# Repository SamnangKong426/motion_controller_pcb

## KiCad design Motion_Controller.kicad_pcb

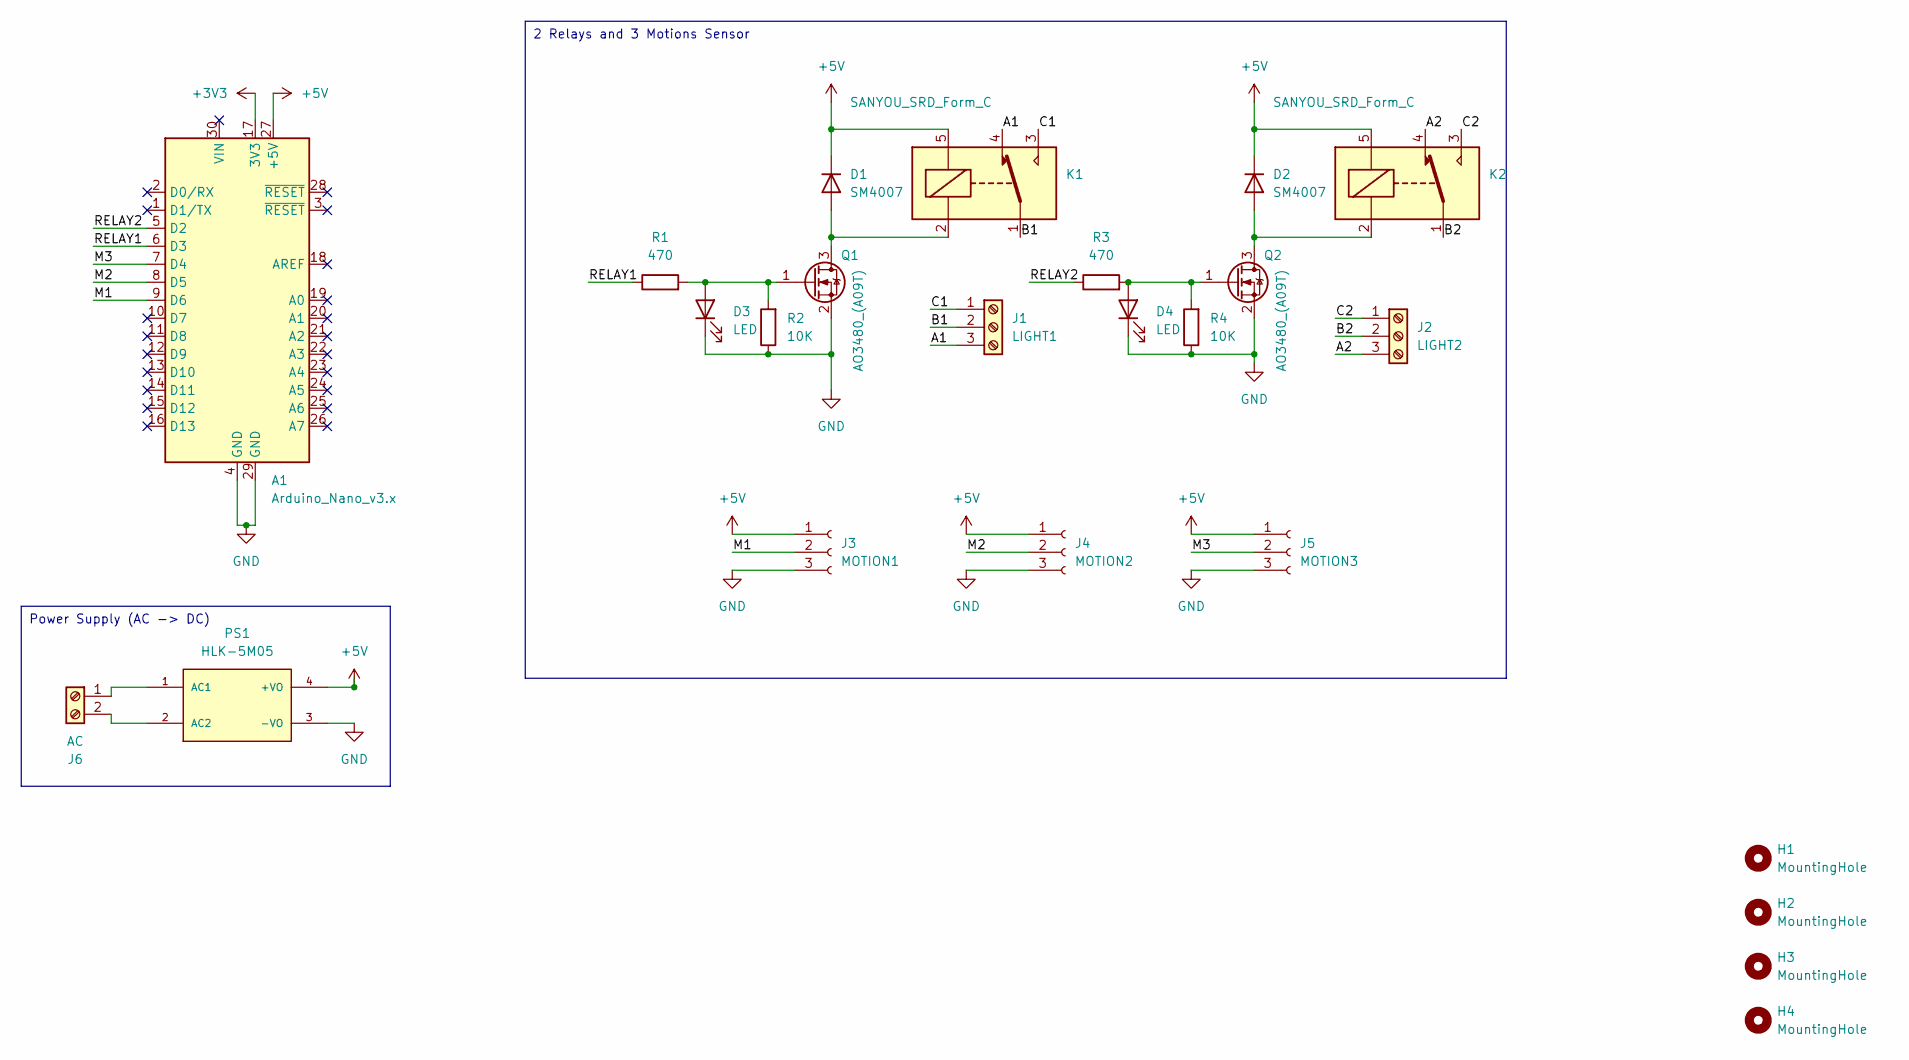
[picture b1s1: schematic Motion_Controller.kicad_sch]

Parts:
A1: Arduino_Nano_v3.x; Arduino_Nano
D1, D2: SM4007; D_SMA
D3, D4: LED; LED_0603_1608Metric
H1, H2, H3, H4: MountingHole; MountingHole_3.2mm_M3_DIN965_Pad
J1: LIGHT1; TerminalBlock_Phoenix_MKDS-1,5-3-5.08_1x03_P5.08mm_Horizont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
J2: LIGHT2; TerminalBlock_Phoenix_MKDS-1,5-3-5.08_1x03_P5.08mm_Horizont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
J3: MOTION1; JST_XH_B3B-XH-A_1x03_P2.50mm_Vertical
J4: MOTION2; JST_XH_B3B-XH-A_1x03_P2.50mm_Vertical
J5: MOTION3; JST_XH_B3B-XH-A_1x03_P2.50mm_Vertical
J6: AC; TerminalBlock_Phoenix_MKDS-1,5-2-5.08_1x02_P5.08mm_Horizont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
K1, K2: SANYOU_SRD_Form_C; Relay_SPDT_SANYOU_SRD_Series_Form_C
PS1: HLK-5M05; CONV_HLK-5M05; PARTREV N/A
Q1, Q2: AO3480_(A09T); SOT-23
R1, R3: 470; R_0603_1608Metric
R2, R4: 10K; R_0603_1608Metric

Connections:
+3V3: A1.17 (3V3)
+5V: A1.27 (+5V), D1.1 (K), D2.1 (K), J3.1, J4.1, J5.1, K1.5, K2.5, PS1.4 (+VO)
/A1: J1.3, K1.4
/A2: J2.3, K2.4
/B1: J1.2, K1.1
/B2: J2.2, K2.1
/C1: J1.1, K1.3
/C2: J2.1, K2.3
/M1: A1.9 (D6), J3.2
/M2: A1.8 (D5), J4.2
/M3: A1.7 (D4), J5.2
/RELAY1: A1.6 (D3), R1.1
/RELAY2: A1.5 (D2), R3.1
GND: A1.4 (GND), A1.29 (GND), D3.1 (K), D4.1 (K), J3.3, J4.3, J5.3, PS1.3 (-VO), Q1.2 (S), Q2.2 (S), R2.1, R4.1
unnamed: D1.2 (A), K1.2, Q1.3 (D)
unnamed: D2.2 (A), K2.2, Q2.3 (D)
unnamed: D3.2 (A), Q1.1 (G), R1.2, R2.2
unnamed: D4.2 (A), Q2.1 (G), R3.2, R4.2
unnamed: J6.1, PS1.1 (AC1)
unnamed: J6.2, PS1.2 (AC2)

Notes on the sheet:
2 Relays and 3 Motions Sensor
Power Supply (AC -> DC)

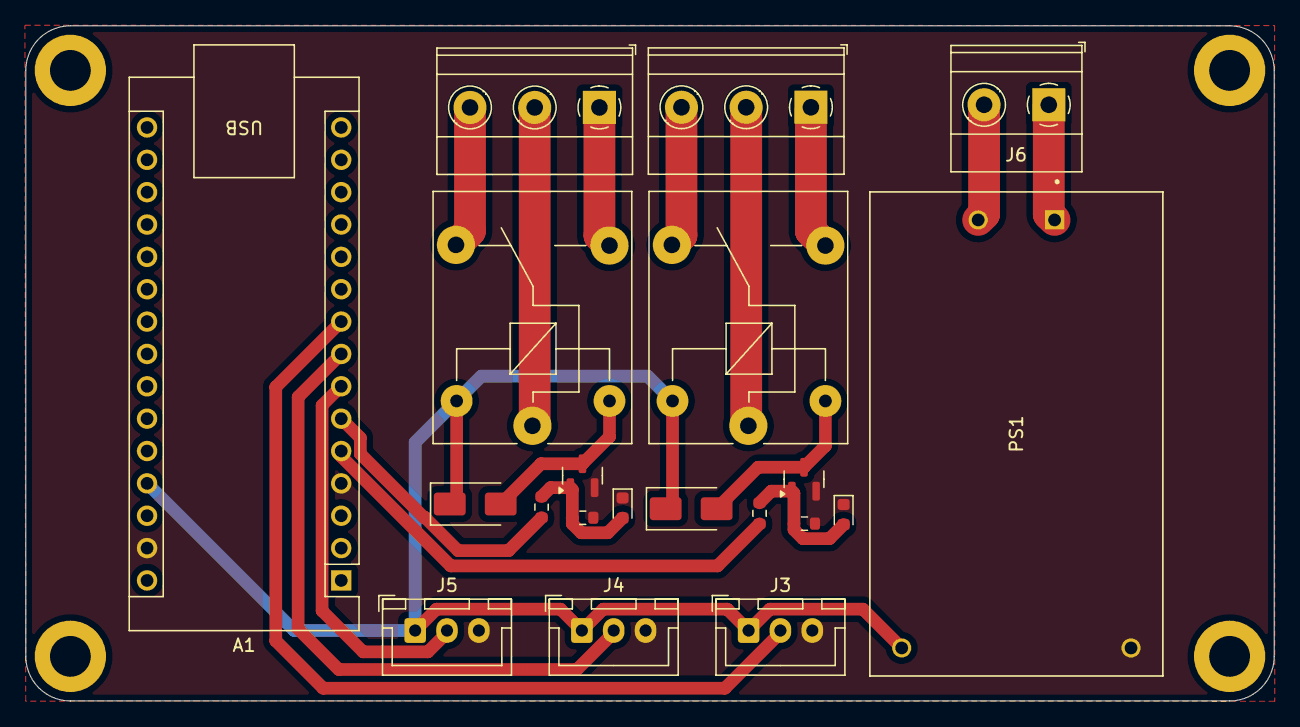
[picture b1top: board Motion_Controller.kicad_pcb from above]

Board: 2 copper layers, 98.0 x 53.0 mm, 24 parts (0 on the bottom side), 19 nets.

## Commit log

2024-09-18 Motion Controller PCB
